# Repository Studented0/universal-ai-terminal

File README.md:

# Universal AI Terminal

A pocketable AI terminal that runs Claude Code and Ollama over LTE. Custom carrier board for a Raspberry Pi Compute Module 5, 7" AMOLED touchscreen, and its own cellular modem so it doesn't need WiFi. While a long prompt is running, you can play a game on it instead of staring at the terminal.

---

## Screenshots

(CNC aluminum Enclosure)

Assembly with enclosure  the switches are also going to be 90 degree switches, not vertical ones (not including display)

---

## Why I built this

I kept wanting Claude Code running when I was away from my desk, and there was no good way to do that besides carrying a laptop everywhere. There are videos all over the internet of people sleeping next to a laptop with Claude Code running waking up to accept permissions, or walking around a grocery store with their laptop open, looking crazy. I wanted something pocketable that solves that.

## Hardware

88×155mm, 4-layer board (JLC04161H-3313 stackup), designed in KiCad 9. Six hierarchical schematic sheets: Power, CM5, Display, Cellular, Audio, Controls.

**Compute** — Raspberry Pi Compute Module 5 (8GB RAM, 64GB eMMC, WiFi). Quad-core Cortex-A76 @ 2.4GHz. 

**Display** — DXQ7D0023, 7" AMOLED, 1080×1920, up to 165Hz variable refresh. ICNA3512 driver IC. FT3519T capacitive touch (FocalTech, I2C address 0x38).  Panel connector is a Hirose FH26-39S-0.3SHW (39-pin, 0.3mm pitch); board side is a 40-pin 0.5mm ZIF (Kinghelm KH-FG0.5-H2.0-40PIN), pins 1-39 mapped straight through, pin 40 unused.

**Cellular** — Quectel EC25AFXGA-MINIPCIE, Cat 4 LTE, AT&T/T-Mobile certified for North America. Mini PCIe form factor so it plugs in rather than getting hand-soldered. Uses USB 2.0 internally, not PCIe.

**Power** — BQ25895 handles battery charging and power path from USB-C input. TPS61235P boosts battery voltage up to the 5V the CM5 needs. FUSB302 negotiates USB-PD for faster charging. Two SGM2036 LDOs step down to 3.3V and 1.8V for the display and peripherals.

**I/O** — Two USB-C ports: one power and USB 2.0 (charging), one full data port with USB 3.0 SuperSpeed and a two-transistor load switch for VBUS control. Three tactile buttons (volume up/down, power; though power itself uses the CM5's dedicated PWR_Button pin and needs no GPIO at all). UART debug header, Test Points for power.

**Battery** — 10,000mAh Li-Po.

---

## Enclosure

3mm black-anodized aluminum plate on the back (CNC machined, doubles as a heatsink and structural backing), a thermal pad between the board and plate, then a bottom shell. 

---

## Software

Raspberry Pi OS Lite (64-bit, Bookworm), headless. 
---

## Bill of Materials

Full itemized BOM across all vendors: [`BOM_Universal_AI_Terminal.csv`](BOM_Universal_AI_Terminal.csv)

---

## Repository Structure

```
universal-ai-terminal/
├── HACK CLUB RELATED.kicad_pro    # KiCad project file 
├── HACK CLUB RELATED.kicad_sch    # schematic
├── HACK CLUB RELATED.kicad_pcb    # PCB layout
├── HACK CLUB RELATED.kicad_prl
├── HACK CLUB RELATED.step         # 3D STEP export of the board
├── power.kicad_sch                # Power sheet
├── CM5.kicad_sch                  # CM5 sheet
├── display.kicad_sch              # Display sheet
├── Cellular.kicad_sch             # Cellular sheet
├── audio.kicad_sch                # Audio sheet
├── controls.kicad_sch             # Controls sheet
├── convert_hlabels.py             # script used to convert hierarchical labels to global 
├── libs/easyeda/                  # imported EasyEDA symbols and footprints
├── production/                    # gerbers, BOM, CPL; JLCPCB Fabrication Toolkit output
├── HACK CLUB RELATED.SLDASM       # SolidWorks enclosure assembly
├── Part8.SLDPRT                   # SolidWorks enclosure part
├── BOM_Universal_AI_Terminal.csv  # full itemized BOM
├── journal.md                     # build log
├── LICENSE
└── README.md
```

`.kicad_sch.bak` files and KiCad's auto-generated `-backups/` folders are local working files, not meant to be tracked — they'll stay out of future commits once `.gitignore` is fixed.

---

## License

[MIT](LICENSE)

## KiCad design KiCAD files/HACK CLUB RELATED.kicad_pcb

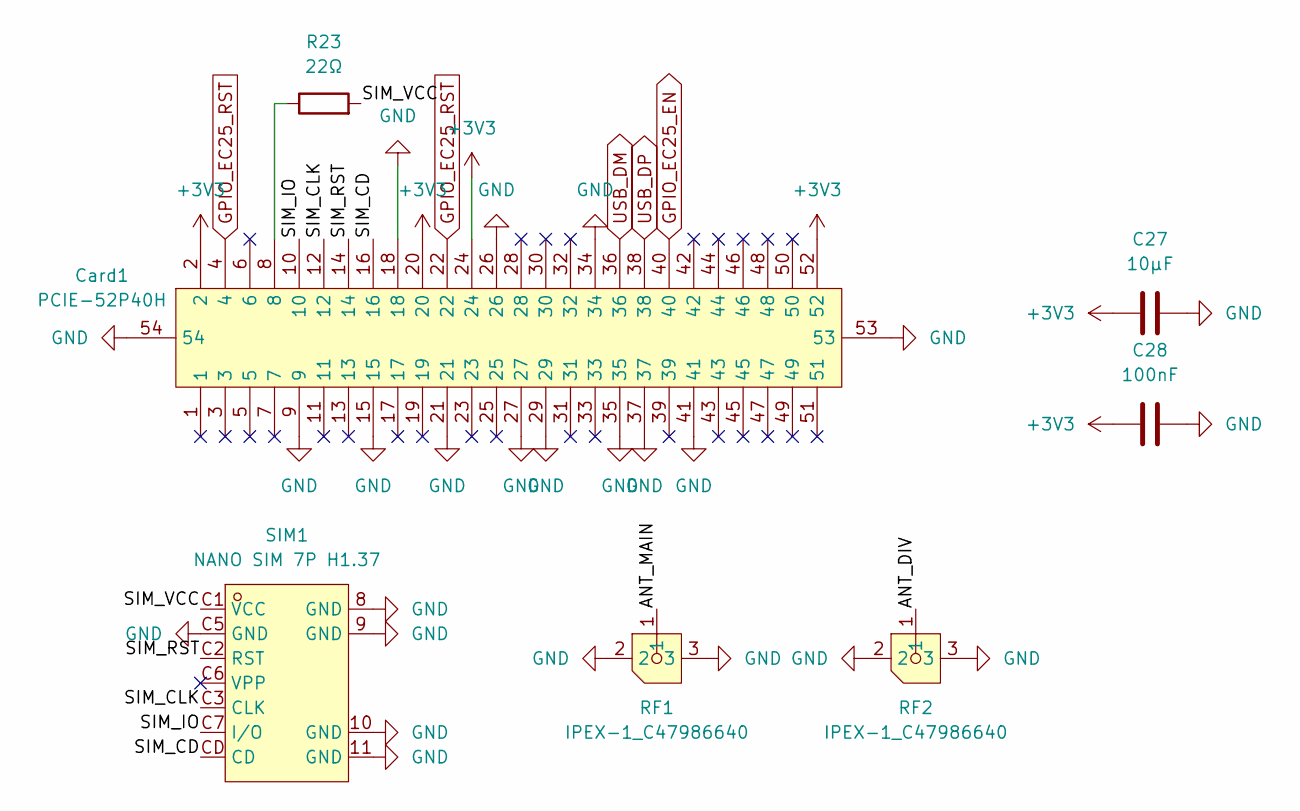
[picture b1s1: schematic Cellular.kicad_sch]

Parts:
C27: 10μF; C_0805_2012Metric
C28: 100nF; C_0402_1005Metric
Card1: PCIE-52P40H; PCIE-SMD_PCIE-52P40H-3.5; MPN PCIE-52P40H; LCSC Part C266898
R23: 22Ω; R_0402_1005Metric
RF1, RF2: IPEX-1_C47986640; IPEX-SMD_3P-L2.6-W2.6-LS3.0_RF1200001R; MPN IPEX-1; LCSC Part C47986640
SIM1: NANO SIM 7P H1.37; SIM-SMD_NANO-SIM-7P-H1.37; MPN NANO SIM 7P H1.37; LCSC Part C7529384

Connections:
+3V3: C27.1, C28.1, Card1.2, Card1.20, Card1.24, Card1.52; also elsewhere on the board
/Cellular/ANT_DIV: RF2.1
/Cellular/ANT_MAIN: RF1.1
/Cellular/SIM_CD: Card1.16, SIM1.CD
/Cellular/SIM_CLK: Card1.12, SIM1.C3 (CLK)
/Cellular/SIM_IO: Card1.10, SIM1.C7 (I/O)
/Cellular/SIM_RST: Card1.14, SIM1.C2 (RST)
/Cellular/SIM_VCC: R23.2, SIM1.C1 (VCC)
GND: C27.2, C28.2, Card1.9, Card1.15, Card1.18, Card1.21, Card1.26, Card1.27, Card1.29, Card1.34, Card1.35, Card1.37, Card1.41, Card1.53, Card1.54, RF1.2, RF1.3, RF2.2, RF2.3, SIM1.8 (GND), SIM1.9 (GND), SIM1.10 (GND), SIM1.11 (GND), SIM1.C5 (GND); also elsewhere on the board
GPIO_EC25_EN: Card1.40; also elsewhere on the board
GPIO_EC25_RST: Card1.4, Card1.22; also elsewhere on the board
unnamed: Card1.8, R23.1
USB_DP: Card1.38; also elsewhere on the board

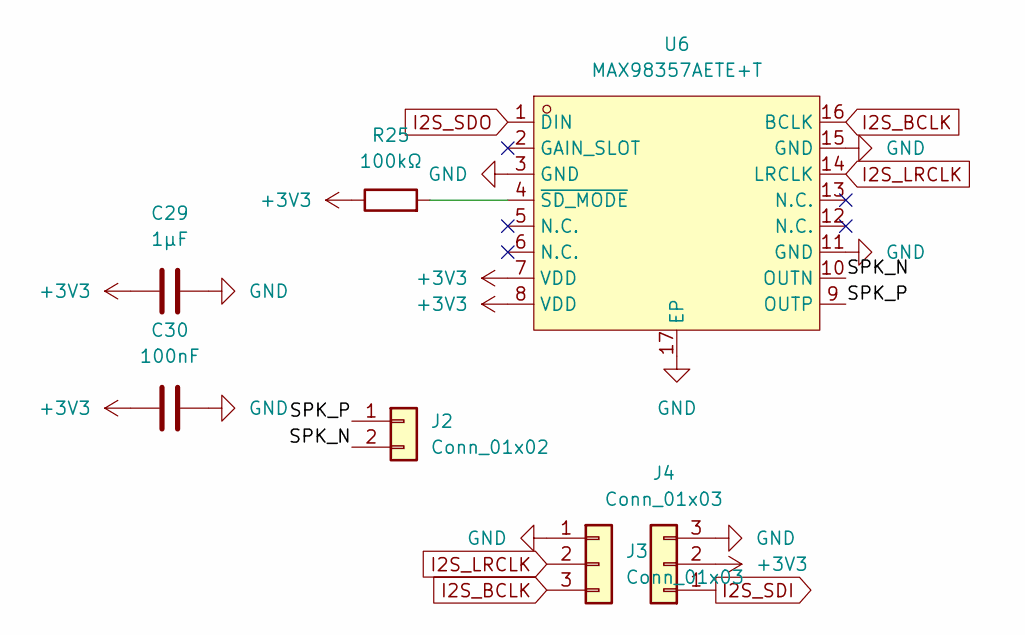
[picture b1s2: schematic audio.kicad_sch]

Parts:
C29: 1μF; C_0402_1005Metric
C30: 100nF; C_0402_1005Metric
J2: Conn_01x02; PinHeader_1x02_P2.54mm_Vertical
J3, J4: Conn_01x03; PinSocket_1x03_P2.54mm_Vertical
R25: 100kΩ; C_0402_1005Metric
U6: MAX98357AETE+T; TQFN-16_L3.0-W3.0-P0.50-BL-EP1.5; MPN MAX98357AETE+T; LCSC Part C910544

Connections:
+3V3: C29.1, C30.1, J4.2, R25.1, U6.7 (VDD), U6.8 (VDD); also elsewhere on the board
/Audio/SPK_N: J2.2, U6.10 (OUTN)
/Audio/SPK_P: J2.1, U6.9 (OUTP)
GND: C29.2, C30.2, J3.1, J4.3, U6.3 (GND), U6.11 (GND), U6.15 (GND), U6.17 (EP); also elsewhere on the board
I2S_BCLK: J3.3, U6.16 (BCLK); also elsewhere on the board
I2S_LRCLK: J3.2, U6.14 (LRCLK)
I2S_SDI: J4.1; also elsewhere on the board
I2S_SDO: U6.1 (DIN); also elsewhere on the board
unnamed: R25.2, U6.4 (~SD_MODE)

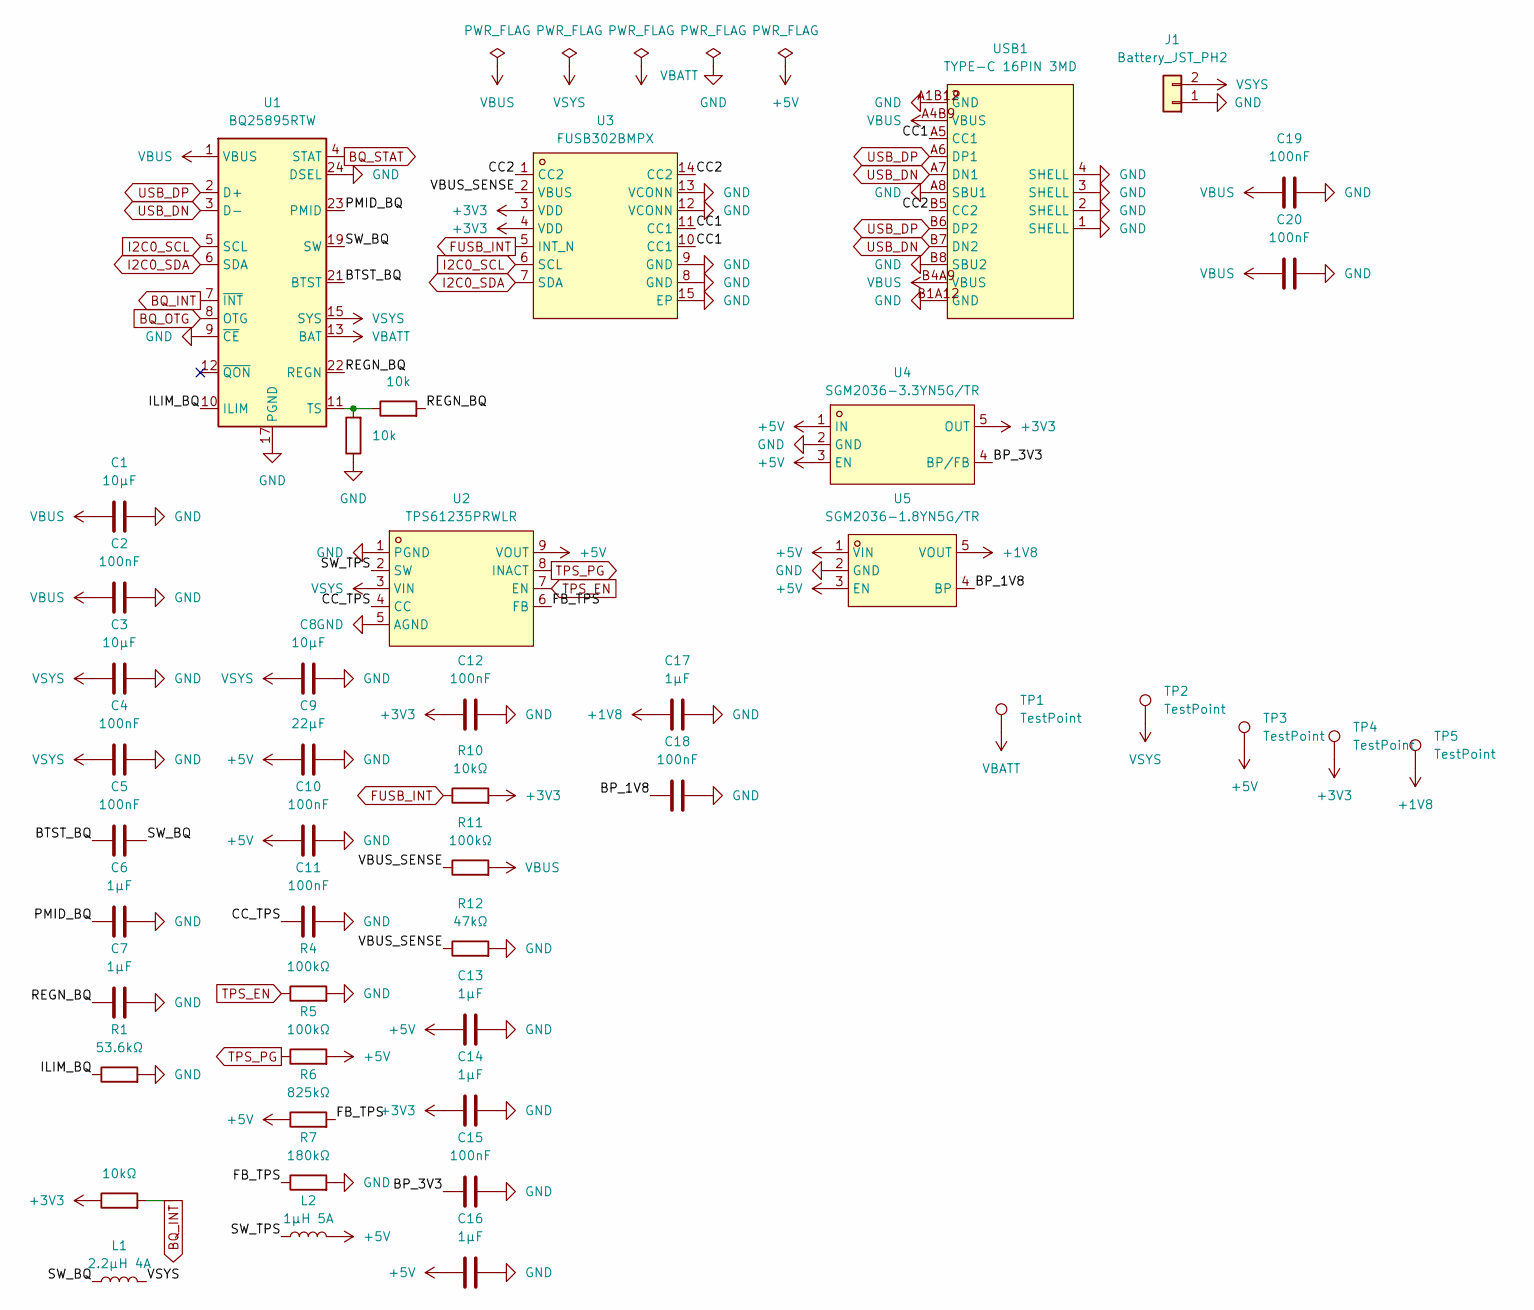
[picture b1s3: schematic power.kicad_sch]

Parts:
C1, C3, C8: 10μF; C_0805_2012Metric
C2, C4, C5, C10, C11, C12, C15, C18, C19, C20: 100nF; C_0402_1005Metric
C6, C7, C13, C14, C16, C17: 1μF; C_0402_1005Metric
C9: 22μF; C_0805_2012Metric
J1: Battery_JST_PH2; JST_PH_S2B-PH-K_1x02_P2.00mm_Horizontal
L1: 2.2μH 4A; L_1210_3225Metric
L2: 1μH 5A; L_1210_3225Metric
R1: 53.6kΩ; R_0402_1005Metric
R3, R10: 10kΩ; R_0402_1005Metric
R4, R5, R11: 100kΩ; R_0402_1005Metric
R6: 825kΩ; R_0402_1005Metric
R7: 180kΩ; R_0402_1005Metric
R8, R9: 10k; R_0402_1005Metric
R12: 47kΩ; R_0402_1005Metric
TP1, TP2, TP3, TP4, TP5: TestPoint; TestPoint_Pad_D1.5mm
U1: BQ25895RTW; Texas_RTW_WQFN-24-1EP_4x4mm_P0.5mm_EP2.7x2.7mm_ThermalVias
U2: TPS61235PRWLR; VQFN-9_L2.5-W2.5-P0.50-TL; MPN TPS61235PRWLR; LCSC Part C544673
U3: FUSB302BMPX; MLP-14_L2.5-W2.5-P0.50-BL-EP; MPN FUSB302BMPX; LCSC Part C132291
U4: SGM2036-3.3YN5G/TR; SOT-23-5_L3.0-W1.7-P0.95-LS2.8-BR; MPN SGM2036-3.3YN5G/TR; LCSC Part C92402
U5: SGM2036-1.8YN5G/TR; SOT-23-5_L2.9-W1.6-P0.95-LS2.8-BR; MPN SGM2036-1.8YN5G/TR; LCSC Part C700371
USB1: TYPE-C 16PIN 3MD; USB-C-SMD_TYPE-C16PIN; MPN TYPE-C 16PIN 3MD(385); LCSC Part C2858270

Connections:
+1V8: C17.1, TP5.1, U5.5 (VOUT); also elsewhere on the board
+3V3: C12.1, C14.1, R3.1, R10.2, TP4.1, U3.3 (VDD), U3.4 (VDD), U4.5 (OUT); also elsewhere on the board
+5V: C9.1, C10.1, C13.1, C16.1, L2.2, R5.2, R6.1, TP3.1, U2.9 (VOUT), U4.1 (IN), U4.3 (EN), U5.1 (VIN), U5.3 (EN); also elsewhere on the board
/Power/BP_1V8: C18.1, U5.4 (BP)
/Power/BP_3V3: C15.1, U4.4 (BP/FB)
/Power/BTST_BQ: C5.1, U1.21 (BTST)
/Power/CC1: U3.10 (CC1), U3.11 (CC1), USB1.A5 (CC1)
/Power/CC2: U3.1 (CC2), U3.14 (CC2), USB1.B5 (CC2)
/Power/CC_TPS: C11.1, U2.4 (CC)
/Power/FB_TPS: R6.2, R7.1, U2.6 (FB)
/Power/ILIM_BQ: R1.1, U1.10 (ILIM)
/Power/PMID_BQ: C6.1, U1.23 (PMID)
/Power/REGN_BQ: C7.1, R9.2, U1.22 (REGN)
/Power/SW_BQ: C5.2, L1.1, U1.19 (SW), U1.20 (SW)
/Power/SW_TPS: L2.1, U2.2 (SW)
/Power/VBUS_SENSE: R11.1, R12.1, U3.2 (VBUS)
BQ_INT: R3.2, U1.7 (~INT); also elsewhere on the board
BQ_OTG: U1.8 (OTG); also elsewhere on the board
BQ_STAT: U1.4 (STAT); also elsewhere on the board
FUSB_INT: R10.1, U3.5 (INT_N); also elsewhere on the board
GND: C1.2, C2.2, C3.2, C4.2, C6.2, C7.2, C8.2, C9.2, C10.2, C11.2, C12.2, C13.2, C14.2, C15.2, C16.2, C17.2, C18.2, C19.2, C20.2, J1.1, R1.2, R4.2, R7.2, R8.1, R12.2, U1.9 (~CE), U1.17 (PGND), U1.18 (PGND), U1.24 (DSEL), U1.25 (PGND), U2.1 (PGND), U2.5 (AGND), U3.8 (GND), U3.9 (GND), U3.12 (VCONN), U3.13 (VCONN), U3.15 (EP), U4.2 (GND), U5.2 (GND), USB1.1 (SHELL), USB1.2 (SHELL), USB1.3 (SHELL), USB1.4 (SHELL), USB1.A1B12 (GND), USB1.A8 (SBU1), USB1.B1A12 (GND), USB1.B8 (SBU2); also elsewhere on the board
I2C0_SCL: U1.5 (SCL), U3.6 (SCL); also elsewhere on the board
I2C0_SDA: U1.6 (SDA), U3.7 (SDA); also elsewhere on the board
unnamed: R8.2, R9.1, U1.11 (TS)
TPS_EN: R4.1, U2.7 (EN); also elsewhere on the board
TPS_PG: R5.1, U2.8 (INACT); also elsewhere on the board
USB_DP: U1.2 (D+), USB1.A6 (DP1), USB1.B6 (DP2); also elsewhere on the board
VBATT: TP1.1, U1.13 (BAT), U1.14 (BAT); also elsewhere on the board
VBUS: C1.1, C2.1, C19.1, C20.1, R11.2, U1.1 (VBUS), USB1.A4B9 (VBUS), USB1.B4A9 (VBUS)
VSYS: C3.1, C4.1, C8.1, J1.2, L1.2, TP2.1, U1.15 (SYS), U1.16 (SYS), U2.3 (VIN)

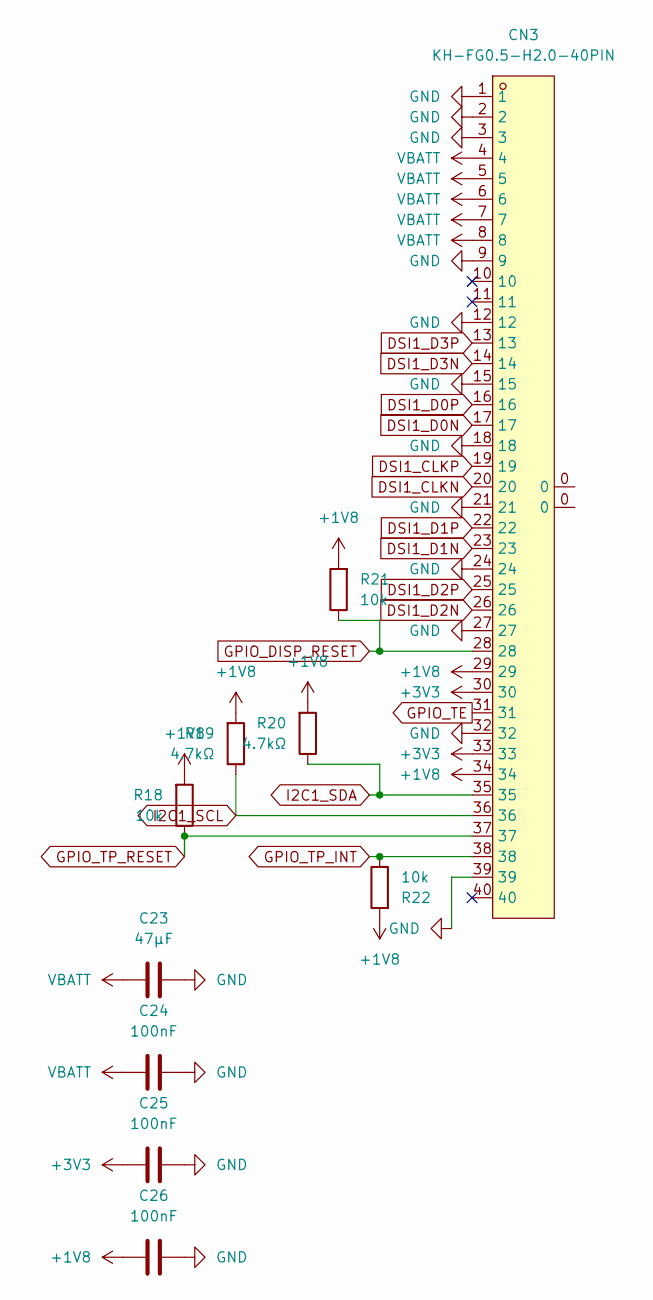
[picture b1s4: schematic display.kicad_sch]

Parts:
C23: 47μF; C_0805_2012Metric
C24, C25, C26: 100nF; C_0402_1005Metric
CN3: KH-FG0.5-H2.0-40PIN; FPC-SMD_40P-P0.50_L5.9-W24.4; MPN KH-FG0.5-H2.0-40PIN; LCSC Part C2797220
R18, R21, R22: 10k; R_0402_1005Metric
R19, R20: 4.7kΩ; R_0402_1005Metric

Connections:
+1V8: C26.1, CN3.29, CN3.34, R18.2, R19.2, R20.2, R21.2, R22.2; also elsewhere on the board
+3V3: C25.1, CN3.30, CN3.33; also elsewhere on the board
DSI1_CLKN: CN3.20; also elsewhere on the board
DSI1_CLKP: CN3.19; also elsewhere on the board
DSI1_D0N: CN3.17; also elsewhere on the board
DSI1_D0P: CN3.16; also elsewhere on the board
DSI1_D1N: CN3.23; also elsewhere on the board
DSI1_D1P: CN3.22; also elsewhere on the board
DSI1_D2N: CN3.26; also elsewhere on the board
DSI1_D2P: CN3.25; also elsewhere on the board
DSI1_D3N: CN3.14; also elsewhere on the board
DSI1_D3P: CN3.13; also elsewhere on the board
GND: C23.2, C24.2, C25.2, C26.2, CN3.1, CN3.2, CN3.3, CN3.9, CN3.12, CN3.15, CN3.18, CN3.21, CN3.24, CN3.27, CN3.32, CN3.39; also elsewhere on the board
GPIO_DISP_RESET: CN3.28, R21.1; also elsewhere on the board
GPIO_TE: CN3.31; also elsewhere on the board
GPIO_TP_INT: CN3.38, R22.1; also elsewhere on the board
GPIO_TP_RESET: CN3.37, R18.1; also elsewhere on the board
I2C1_SCL: CN3.36, R19.1; also elsewhere on the board
I2C1_SDA: CN3.35, R20.1; also elsewhere on the board
VBATT: C23.1, C24.1, CN3.4, CN3.5, CN3.6, CN3.7, CN3.8; also elsewhere on the board

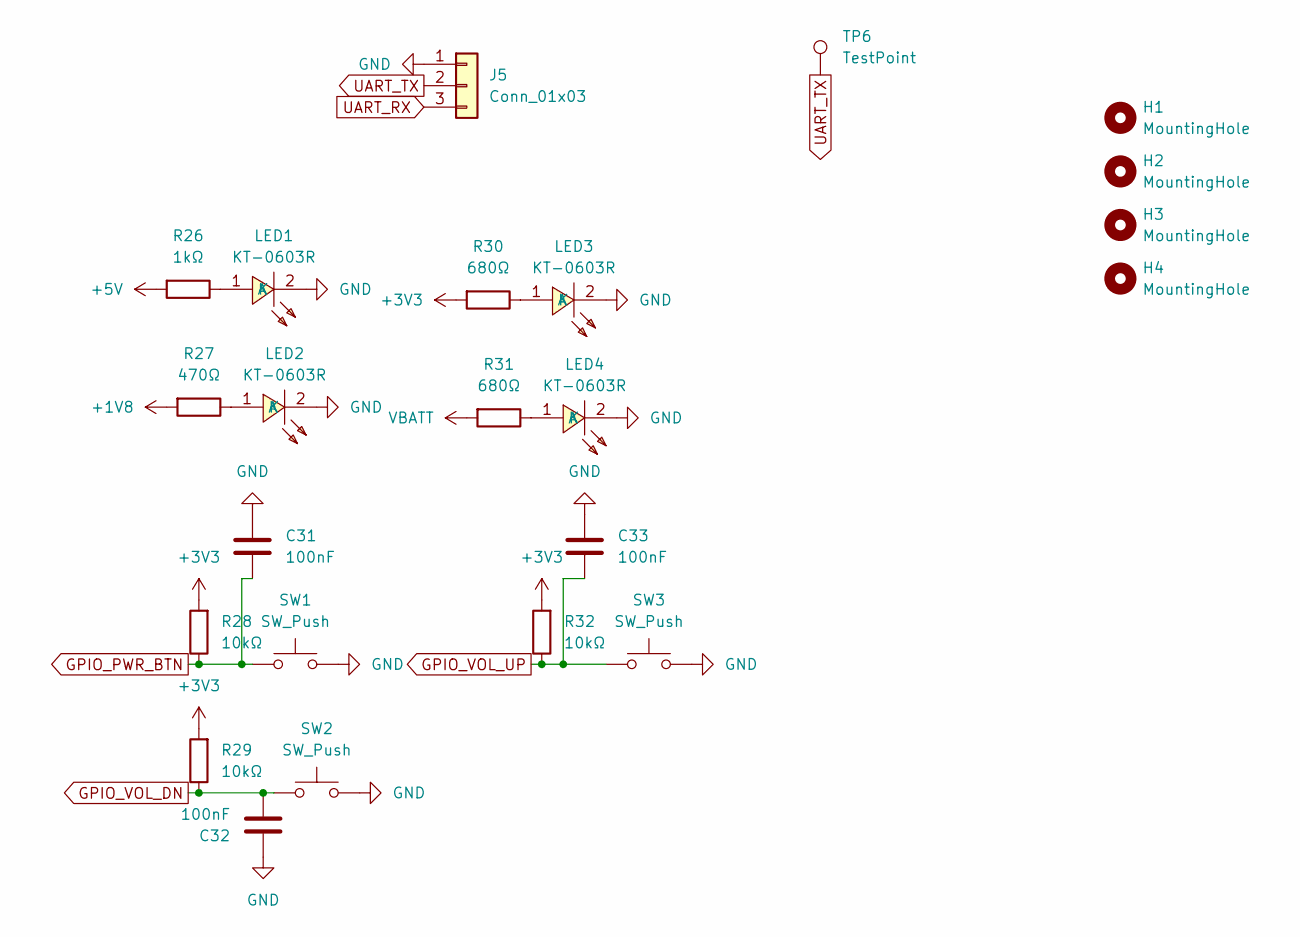
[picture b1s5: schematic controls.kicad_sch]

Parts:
C31, C32, C33: 100nF; C_0402_1005Metric
H1, H2, H3, H4: MountingHole; MountingHole_2.2mm_M2
J5: Conn_01x03; PinHeader_1x03_P2.54mm_Vertical
LED1, LED2, LED3, LED4: KT-0603R; LED-SMD_L1.6-W0.8-R-RD; MPN KT-0603R; LCSC Part C2286
R26: 1kΩ; R_0402_1005Metric
R27: 470Ω; R_0402_1005Metric
R28, R29, R32: 10kΩ; R_0402_1005Metric
R30, R31: 680Ω; R_0402_1005Metric
SW1, SW2, SW3: SW_Push; SW_PUSH_6mm_H5mm
TP6: TestPoint; TestPoint_Pad_D1.5mm

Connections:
+1V8: R27.2; also elsewhere on the board
+3V3: R28.2, R29.2, R30.2, R32.2; also elsewhere on the board
+5V: R26.2; also elsewhere on the board
GND: C31.1, C32.1, C33.1, J5.1, LED1.2 (K), LED2.2 (K), LED3.2 (K), LED4.2 (K), SW1.2, SW2.2, SW3.2; also elsewhere on the board
GPIO_PWR_BTN: C31.2, R28.1, SW1.1; also elsewhere on the board
GPIO_VOL_DN: C32.2, R29.1, SW2.1; also elsewhere on the board
GPIO_VOL_UP: C33.2, R32.1, SW3.1; also elsewhere on the board
unnamed: LED1.1 (A), R26.1
unnamed: LED2.1 (A), R27.1
unnamed: LED3.1 (A), R30.1
unnamed: LED4.1 (A), R31.1
UART_RX: J5.3; also elsewhere on the board
UART_TX: J5.2, TP6.1; also elsewhere on the board
VBATT: R31.2; also elsewhere on the board

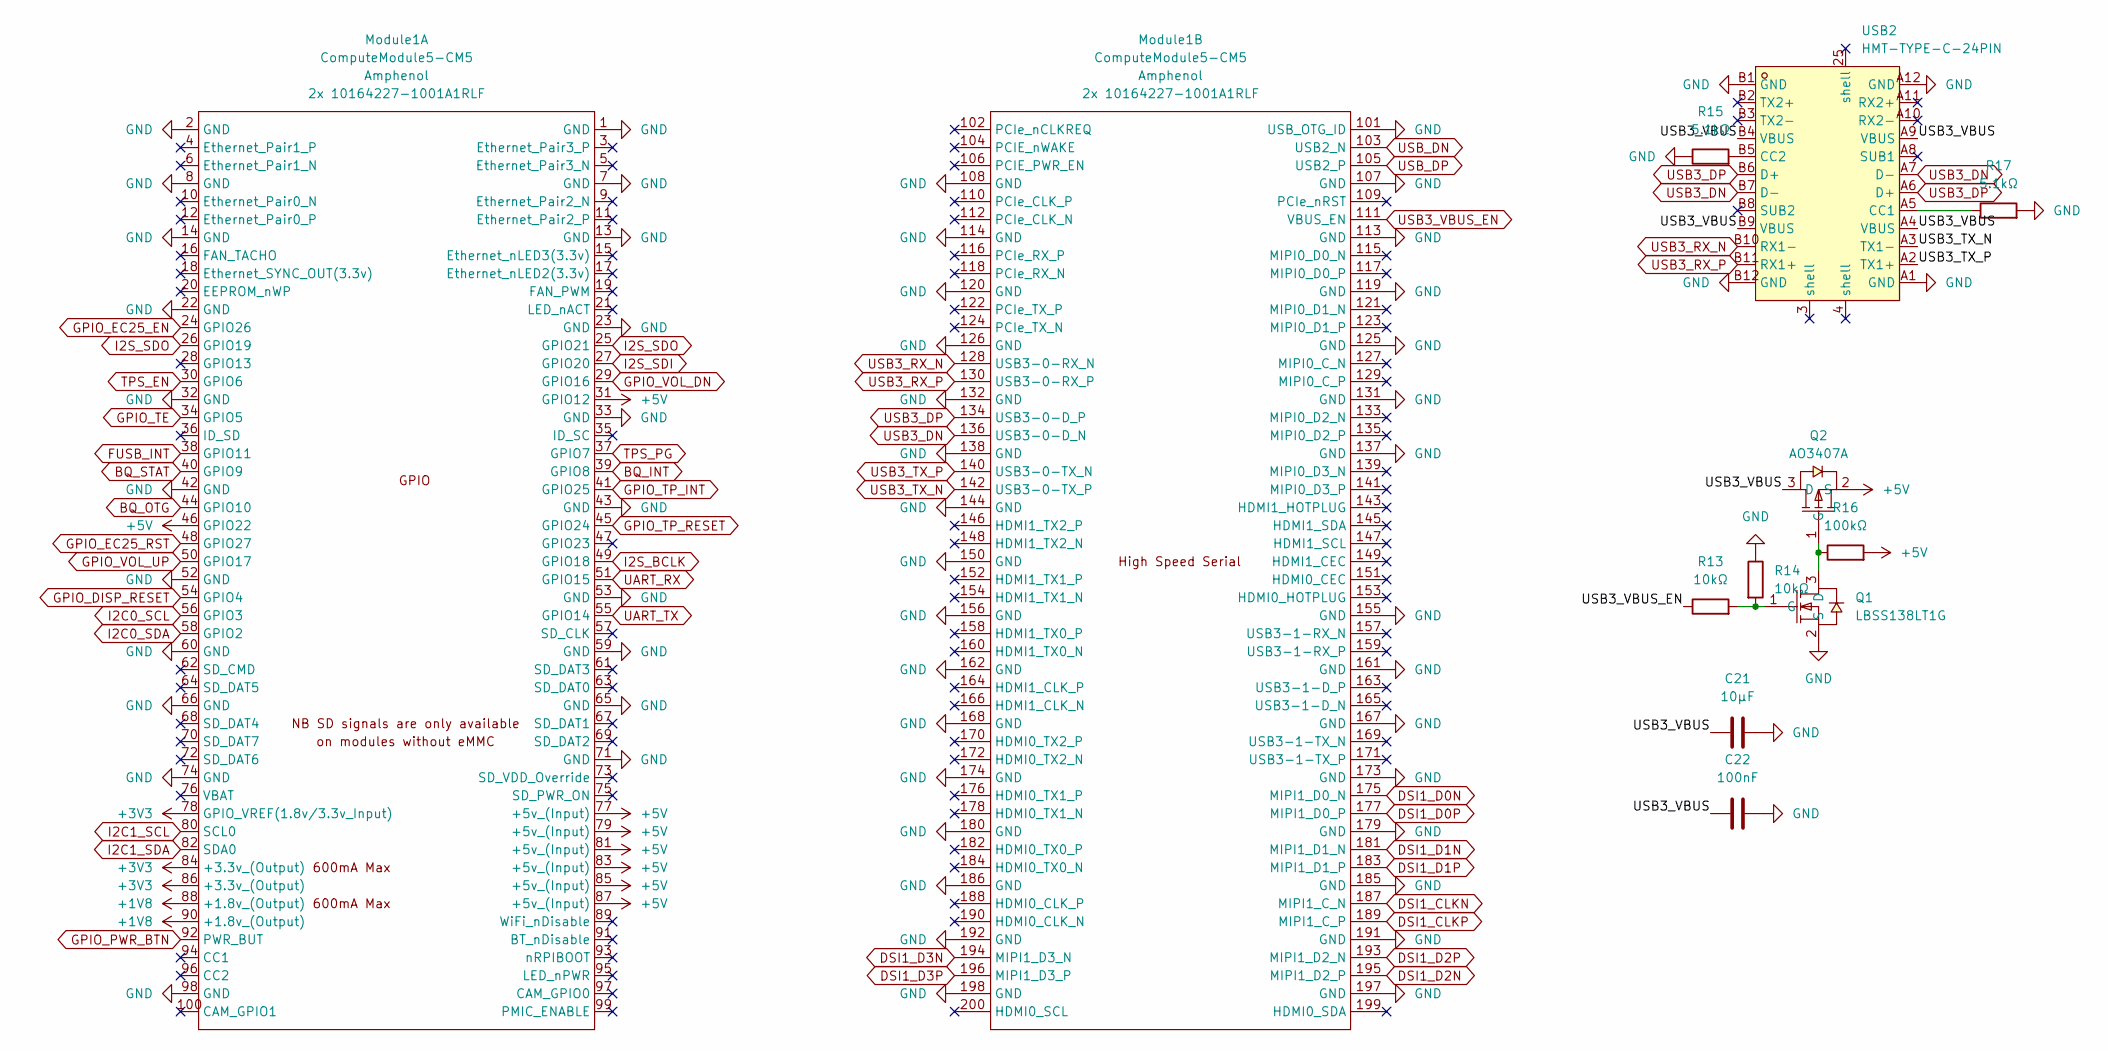
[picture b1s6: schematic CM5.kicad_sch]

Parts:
C21: 10μF; C_0805_2012Metric
C22: 100nF; C_0402_1005Metric
Module1: ComputeModule5-CM5; Raspberry-Pi-5-Compute-Module
Q1: LBSS138LT1G; SOT-23_L2.9-W1.3-P1.90-LS2.4-BR; MPN LBSS138LT1G; LCSC Part C8490
Q2: AO3407A; SOT-23-3_L2.9-W1.6-P1.90-LS2.8-BR; MPN AO3407A; LCSC Part C15155
R13, R14: 10kΩ; R_0402_1005Metric
R15, R17: 5.1kΩ; R_0402_1005Metric
R16: 100kΩ; R_0402_1005Metric
USB2: HMT-TYPE-C-24PIN; USB-C-SMD_TYPE-C-24P-QT; MPN HMT-TYPE-C-24PIN; LCSC Part C53121393

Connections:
+1V8: Module1.88 (+1.8v_(Output)), Module1.90 (+1.8v_(Output)); also elsewhere on the board
+3V3: Module1.78 (GPIO_VREF(1.8v/3.3v_Input)), Module1.84 (+3.3v_(Output)), Module1.86 (+3.3v_(Output)); also elsewhere on the board
+5V: Module1.31 (GPIO12), Module1.46 (GPIO22), Module1.77 (+5v_(Input)), Module1.79 (+5v_(Input)), Module1.81 (+5v_(Input)), Module1.83 (+5v_(Input)), Module1.85 (+5v_(Input)), Module1.87 (+5v_(Input)), Q2.2 (S), R16.2; also elsewhere on the board
/CM5/USB3_VBUS: C21.1, C22.1, Q2.3 (D), USB2.A4 (VBUS), USB2.A9 (VBUS), USB2.B4 (VBUS), USB2.B9 (VBUS)
BQ_INT: Module1.39 (GPIO8); also elsewhere on the board
BQ_OTG: Module1.44 (GPIO10); also elsewhere on the board
BQ_STAT: Module1.40 (GPIO9); also elsewhere on the board
DSI1_CLKN: Module1.187 (MIPI1_C_N); also elsewhere on the board
DSI1_CLKP: Module1.189 (MIPI1_C_P); also elsewhere on the board
DSI1_D0N: Module1.175 (MIPI1_D0_N); also elsewhere on the board
DSI1_D0P: Module1.177 (MIPI1_D0_P); also elsewhere on the board
DSI1_D1N: Module1.181 (MIPI1_D1_N); also elsewhere on the board
DSI1_D1P: Module1.183 (MIPI1_D1_P); also elsewhere on the board
DSI1_D2N: Module1.195 (MIPI1_D2_P); also elsewhere on the board
DSI1_D2P: Module1.193 (MIPI1_D2_N); also elsewhere on the board
DSI1_D3N: Module1.194 (MIPI1_D3_N); also elsewhere on the board
DSI1_D3P: Module1.196 (MIPI1_D3_P); also elsewhere on the board
FUSB_INT: Module1.38 (GPIO11); also elsewhere on the board
GND: C21.2, C22.2, Module1.1 (GND), Module1.2 (GND), Module1.7 (GND), Module1.8 (GND), Module1.13 (GND), Module1.14 (GND), Module1.22 (GND), Module1.23 (GND), Module1.32 (GND), Module1.33 (GND), Module1.42 (GND), Module1.43 (GND), Module1.52 (GND), Module1.53 (GND), Module1.59 (GND), Module1.60 (GND), Module1.65 (GND), Module1.66 (GND), Module1.71 (GND), Module1.74 (GND), Module1.98 (GND), Module1.101 (USB_OTG_ID), Module1.107 (GND), Module1.108 (GND), Module1.113 (GND), Module1.114 (GND), Module1.119 (GND), Module1.120 (GND), Module1.125 (GND), Module1.126 (GND), Module1.131 (GND), Module1.132 (GND), Module1.137 (GND), Module1.138 (GND), Module1.144 (GND), Module1.150 (GND), Module1.155 (GND), Module1.156 (GND), Module1.161 (GND), Module1.162 (GND), Module1.167 (GND), Module1.168 (GND), Module1.173 (GND), Module1.174 (GND), Module1.179 (GND), Module1.180 (GND), Module1.185 (GND), Module1.186 (GND), Module1.191 (GND), Module1.192 (GND), Module1.197 (GND), Module1.198 (GND), Q1.2 (S), R14.1, R15.1, R17.2, USB2.A1 (GND), USB2.A12 (GND), USB2.B1 (GND), USB2.B12 (GND); also elsewhere on the board
GPIO_DISP_RESET: Module1.54 (GPIO4); also elsewhere on the board
GPIO_EC25_EN: Module1.24 (GPIO26); also elsewhere on the board
GPIO_EC25_RST: Module1.48 (GPIO27); also elsewhere on the board
GPIO_PWR_BTN: Module1.92 (PWR_BUT); also elsewhere on the board
GPIO_TE: Module1.34 (GPIO5); also elsewhere on the board
GPIO_TP_INT: Module1.41 (GPIO25); also elsewhere on the board
GPIO_TP_RESET: Module1.45 (GPIO24); also elsewhere on the board
GPIO_VOL_DN: Module1.29 (GPIO16); also elsewhere on the board
GPIO_VOL_UP: Module1.50 (GPIO17); also elsewhere on the board
I2C0_SCL: Module1.56 (GPIO3); also elsewhere on the board
I2C0_SDA: Module1.58 (GPIO2); also elsewhere on the board
I2C1_SCL: Module1.80 (SCL0); also elsewhere on the board
I2C1_SDA: Module1.82 (SDA0); also elsewhere on the board
I2S_BCLK: Module1.49 (GPIO18); also elsewhere on the board
I2S_SDI: Module1.27 (GPIO20); also elsewhere on the board
I2S_SDO: Module1.25 (GPIO21), Module1.26 (GPIO19); also elsewhere on the board
unnamed: Q1.3 (D), Q2.1 (G), R16.1
unnamed: Q1.1 (G), R13.2, R14.2
unnamed: R17.1, USB2.A5 (CC1)
unnamed: R15.2, USB2.B5 (CC2)
TPS_EN: Module1.30 (GPIO6); also elsewhere on the board
TPS_PG: Module1.37 (GPIO7); also elsewhere on the board
UART_RX: Module1.51 (GPIO15); also elsewhere on the board
UART_TX: Module1.55 (GPIO14); also elsewhere on the board
USB3_DN: Module1.136 (USB3-0-D_N), USB2.A7 (D-), USB2.B7 (D-)
USB3_DP: Module1.134 (USB3-0-D_P), USB2.A6 (D+), USB2.B6 (D+)
USB3_RX_N: Module1.128 (USB3-0-RX_N), USB2.B10 (RX1-)
USB3_RX_P: Module1.130 (USB3-0-RX_P), USB2.B11 (RX1+)
USB3_TX_N: Module1.142 (USB3-0-TX_P), USB2.A3 (TX1-)
USB3_TX_P: Module1.140 (USB3-0-TX_N), USB2.A2 (TX1+)
USB3_VBUS_EN: Module1.111 (VBUS_EN), R13.1
USB_DP: Module1.105 (USB2_P); also elsewhere on the board

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
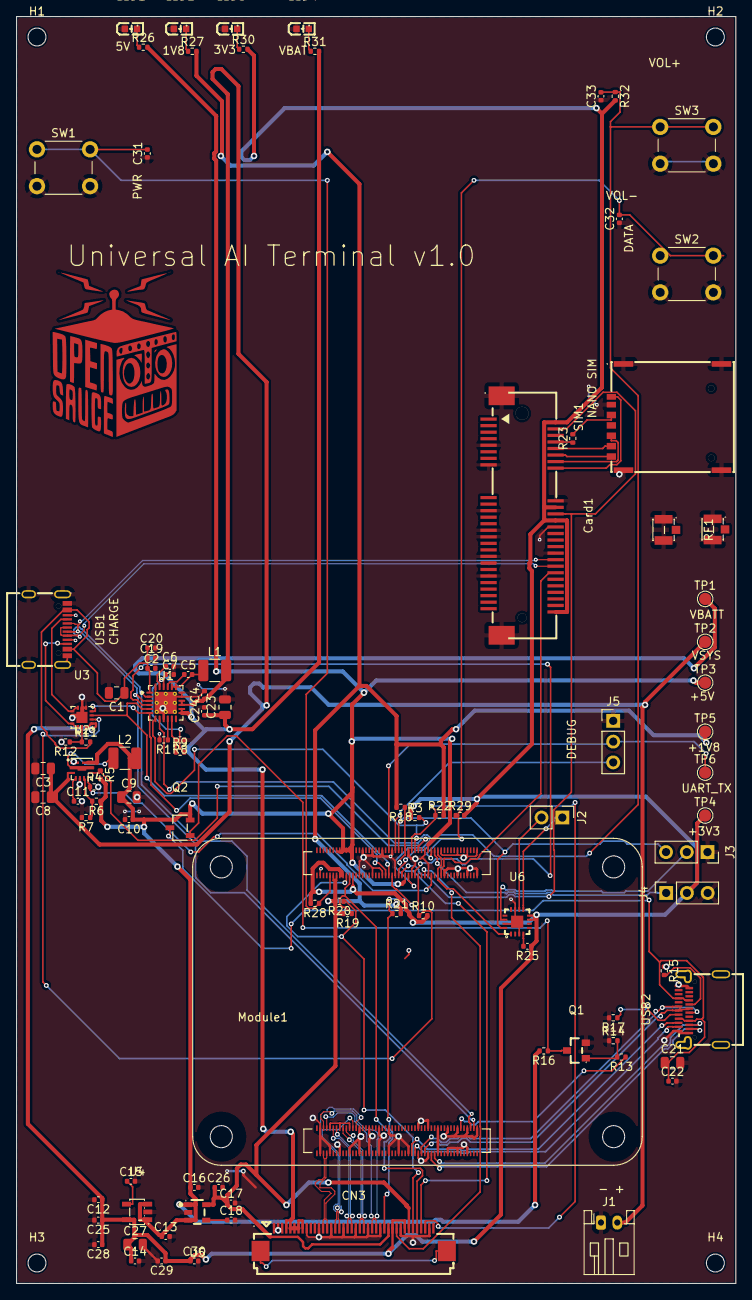
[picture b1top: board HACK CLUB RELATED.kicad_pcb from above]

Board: 4 copper layers, 88.0 x 155.0 mm, 103 parts (0 on the bottom side), 83 nets.

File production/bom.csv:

Designator,Footprint,Quantity,Value,LCSC Part #
"C1, C21, C27, C3, C8",0805,5,10μF,
"C10, C11, C12, C15, C18, C19, C2, C20, C22, C24, C25, C26, C28, C30, C31, C32, C33, C4, C5",0402,19,100nF,
"C13, C14, C16, C17, C29, C6, C7",0402,7,1μF,
C23,0805,1,47μF,
C9,0805,1,22μF,
CARD1,PCIE-SMD_PCIE-52P40H-3.5,1,PCIE-52P40H,C266898
CN3,FPC-SMD_40P-P0.50_L5.9-W24.4,1,KH-FG0.5-H2.0-40PIN,C2797220
J1,JST_PH_S2B-PH-K_1x02_P2.00mm_Horizontal,1,Battery_JST_PH2,
J2,PinHeader_1x02_P2.54mm_Vertical,1,Conn_01x02,
"J3, J4",PinSocket_1x03_P2.54mm_Vertical,2,Conn_01x03,
J5,PinHeader_1x03_P2.54mm_Vertical,1,Conn_01x03,
L1,1210,1,2.2μH 4A,
L2,1210,1,1μH 5A,
"LED1, LED2, LED3, LED4",LED-SMD_L1.6-W0.8-R-RD,4,KT-0603R,C2286
MODULE1,Raspberry-Pi-5-Compute-Module,1,ComputeModule5-CM5,
Q1,SOT-23_L2.9-W1.3-P1.90-LS2.4-BR,1,LBSS138LT1G,C8490
Q2,SOT-23-3_L2.9-W1.6-P1.90-LS2.8-BR,1,AO3407A,C15155
R1,0402,1,53.6kΩ,
"R10, R13, R14, R28, R29, R3, R32",0402,7,10kΩ,
"R11, R16, R25, R4, R5",0402,5,100kΩ,
R12,0402,1,47kΩ,
"R15, R17",0402,2,5.1kΩ,
"R18, R21, R22, R8, R9",0402,5,10k,
"R19, R20",0402,2,4.7kΩ,
R23,0402,1,22Ω,
R26,0402,1,1kΩ,
R27,0402,1,470Ω,
"R30, R31",0402,2,680Ω,
R6,0402,1,825kΩ,
R7,0402,1,180kΩ,
"RF1, RF2",IPEX-SMD_3P-L2.6-W2.6-LS3.0_RF1200001R,2,IPEX-1_C47986640,C47986640
SIM1,SIM-SMD_NANO-SIM-7P-H1.37,1,NANO SIM 7P H1.37,C7529384
"SW1, SW2, SW3",SW_PUSH_6mm_H5mm,3,SW_Push,
"TP1, TP2, TP3, TP4, TP5, TP6",TestPoint_Pad_D1.5mm,6,TestPoint,
U1,Texas_RTW_WQFN-24-1EP_4x4mm_P0.5mm_EP2.7x2.7mm_ThermalVias,1,BQ25895RTW,
U2,VQFN-9_L2.5-W2.5-P0.50-TL,1,TPS61235PRWLR,C544673
U3,MLP-14_L2.5-W2.5-P0.50-BL-EP,1,FUSB302BMPX,C132291
U4,SOT-23-5_L3.0-W1.7-P0.95-LS2.8-BR,1,SGM2036-3.3YN5G/TR,C92402
U5,SOT-23-5_L2.9-W1.6-P0.95-LS2.8-BR,1,SGM2036-1.8YN5G/TR,C700371
U6,TQFN-16_L3.0-W3.0-P0.50-BL-EP1.5,1,MAX98357AETE+T,C910544
USB1,USB-C-SMD_TYPE-C16PIN,1,TYPE-C 16PIN 3MD,C2858270
USB2,USB-C-SMD_TYPE-C-24P-QT,1,HMT-TYPE-C-24PIN,C53121393

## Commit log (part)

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2026-06-22 Keep README empty for now
2026-06-22 Remove Untitled-1.py
2026-06-29 Initial commit: schematics, PCB layout, BOM
2026-06-30 Revise journal entries for project updates
    Updated journal entries for project progress, including parts selection, display research, schematic design, PCB layout, and cost estimates. Adjusted details for clarity and accuracy.
2026-06-30 Revise PCB layout and document changes
    Updated PCB layout details, including MIPI DSI routing challenges and physical stack configuration. Added images for visual reference.
2026-06-30 Rename journal_finalfinal.md to journal.md
2026-06-30 Fix gitignore filename
2026-06-30 Add README for Universal AI Terminal project
    Added detailed information about the Universal AI Terminal, including hardware specifications, software setup, and repository structure.
2026-06-30 Update BOM with new components and totals
2026-06-30 Adjust total values and refine PMD Way description
    fixed parsing error
2026-06-30 Update README with project details and images
2026-06-30 Reorganize repository structure
2026-06-30 Revise journal entries for grammar and clarity
    Corrected various grammatical errors and improved clarity in journal entries. Updated details regarding component specifications and design changes.
